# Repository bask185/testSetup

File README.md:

test hardware for XpressNet atm (May contain loconet?)

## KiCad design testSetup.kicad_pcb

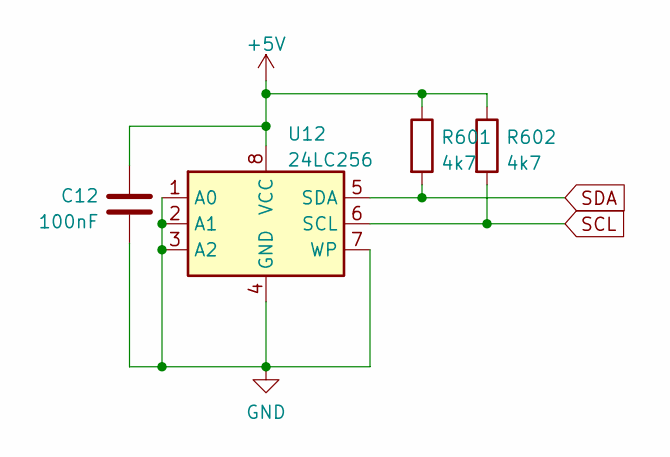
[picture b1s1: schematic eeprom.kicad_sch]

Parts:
C12: 100nF; C_0805_2012Metric_Pad1.18x1.45mm_HandSolder; JLCPCB Part# C14663
R601, R602: 4k7; R_0805_2012Metric_Pad1.20x1.40mm_HandSolder; JLCPCB Part# C23162
U12: 24LC256; DIP-8_W7.62mm; JLCPCB Part# C2987263

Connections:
+5V: C12.2, R601.1, R602.1, U12.8 (VCC); also elsewhere on the board
GND: C12.1, U12.1 (A0), U12.2 (A1), U12.3 (A2), U12.4 (GND), U12.7 (WP); also elsewhere on the board
SCL: R602.2, U12.6 (SCL); also elsewhere on the board
SDA: R601.2, U12.5 (SDA); also elsewhere on the board

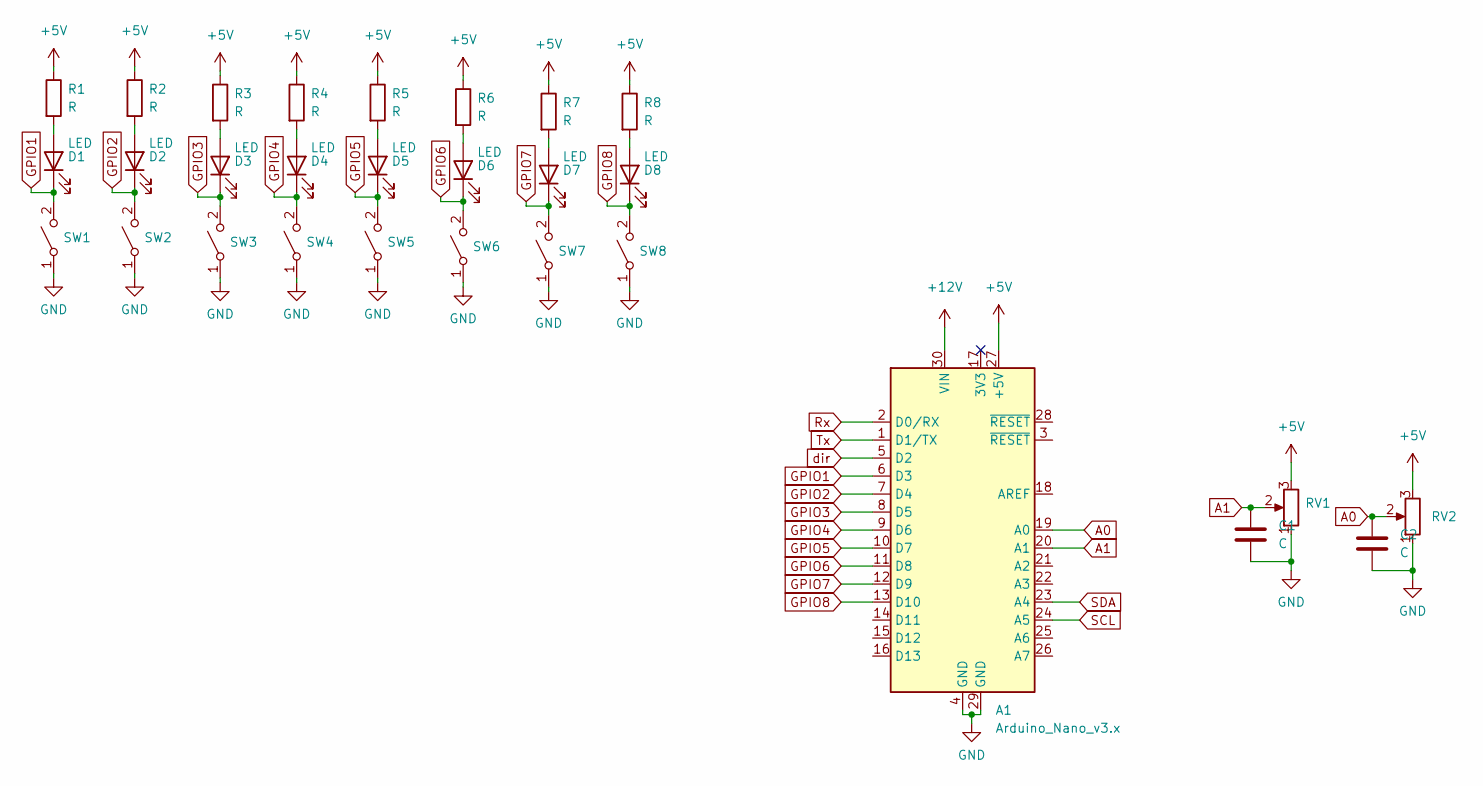
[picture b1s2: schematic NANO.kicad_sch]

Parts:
A1: Arduino_Nano_v3.x; Arduino_Nano
C1, C2: C; C_0805_2012Metric_Pad1.18x1.45mm_HandSolder
D1, D2, D3, D4, D5, D6, D7, D8: LED; LED_D3.0mm
R1, R2, R3, R4, R5, R6, R7, R8: R; R_0805_2012Metric_Pad1.20x1.40mm_HandSolder
RV1, RV2: R_Potentiometer; Potentiometer_Piher_PT-10-V10_Vertical
SW1, SW2, SW3, SW4, SW5, SW6, SW7, SW8: SW_SPST; SW_PUSH_6mm_H4.3mm

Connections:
+5V: A1.27 (+5V), R1.1, R2.1, R3.1, R4.1, R5.1, R6.1, R7.1, R8.1, RV1.3, RV2.3; also elsewhere on the board
+12V: A1.30 (VIN); also elsewhere on the board
A0: A1.19 (A0), C2.1, RV2.2
A1: A1.20 (A1), C1.1, RV1.2
GND: A1.4 (GND), A1.29 (GND), C1.2, C2.2, RV1.1, RV2.1, SW1.1 (A), SW2.1 (A), SW3.1 (A), SW4.1 (A), SW5.1 (A), SW6.1 (A), SW7.1 (A), SW8.1 (A); also elsewhere on the board
GPIO1: A1.6 (D3), D1.1 (K), SW1.2 (B)
GPIO2: A1.7 (D4), D2.1 (K), SW2.2 (B)
GPIO3: A1.8 (D5), D3.1 (K), SW3.2 (B)
GPIO4: A1.9 (D6), D4.1 (K), SW4.2 (B)
GPIO5: A1.10 (D7), D5.1 (K), SW5.2 (B)
GPIO6: A1.11 (D8), D6.1 (K), SW6.2 (B)
GPIO7: A1.12 (D9), D7.1 (K), SW7.2 (B)
GPIO8: A1.13 (D10), D8.1 (K), SW8.2 (B)
unnamed: D1.2 (A), R1.2
unnamed: D2.2 (A), R2.2
unnamed: D3.2 (A), R3.2
unnamed: D4.2 (A), R4.2
unnamed: D5.2 (A), R5.2
unnamed: D6.2 (A), R6.2
unnamed: D7.2 (A), R7.2
unnamed: D8.2 (A), R8.2
Rx: A1.2 (D0/RX); also elsewhere on the board
SCL: A1.24 (A5); also elsewhere on the board
SDA: A1.23 (A4); also elsewhere on the board
Tx: A1.1 (D1/TX); also elsewhere on the board
dir: A1.5 (D2); also elsewhere on the board

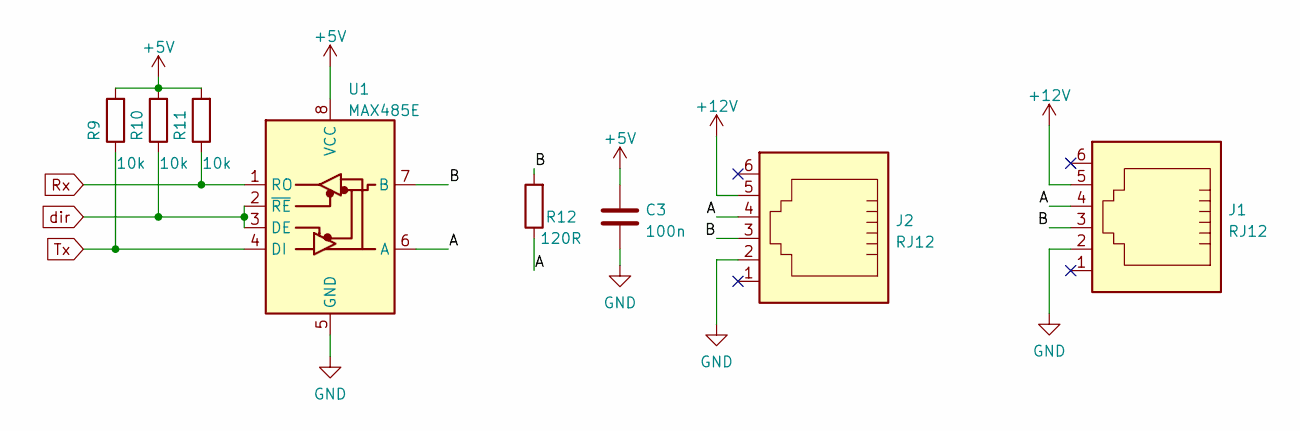
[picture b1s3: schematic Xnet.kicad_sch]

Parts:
C3: 100n; C_0805_2012Metric_Pad1.18x1.45mm_HandSolder
J1, J2: RJ12; RJ12_Amphenol_54601
R9, R10, R11: 10k; R_0805_2012Metric_Pad1.20x1.40mm_HandSolder
R12: 120R; R_0805_2012Metric_Pad1.20x1.40mm_HandSolder
U1: MAX485E; DIP-8_W7.62mm

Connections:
+5V: C3.1, R9.2, R10.2, R11.2, U1.8 (VCC); also elsewhere on the board
+12V: J1.5, J2.5; also elsewhere on the board
/Xnet/A: J1.4, J2.4, R12.1, U1.6 (A)
/Xnet/B: J1.3, J2.3, R12.2, U1.7 (B)
GND: C3.2, J1.2, J2.2, U1.5 (GND); also elsewhere on the board
Rx: R11.1, U1.1 (RO); also elsewhere on the board
Tx: R9.1, U1.4 (DI); also elsewhere on the board
dir: R10.1, U1.2 (~RE), U1.3 (DE); also elsewhere on the board

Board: 2 copper layers, 41 parts (0 on the bottom side), 28 nets, no tracks yet.
